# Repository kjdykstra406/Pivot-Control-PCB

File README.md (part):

"# Pivot-Control-P(kicad_sch
	(version 20250114)
	(generator "eeschema")
	(generator_version "9.0")
	(uuid "5632ba6c-34ff-4a54-b5e1-022e30e0e773")
	(paper "A0")
	(lib_symbols
		(symbol "Adafruit I2C to 8 Channel Solenoid Driver-eagle-import:DIODE-SCHOTTKYSOD-323"
			(exclude_from_sim no)
			(in_bom yes)
			(on_board yes)
			(property "Reference" "D"
				(at 0 2.54 0)
				(effects
					(font
						(size 1.27 1.0795)
					)
				)
			)
			(property "Value" ""
				(at 0 -2.5 0)
				(effects
					(font
						(size 1.27 1.0795)
					)
				)
			)
			(property "Footprint" "Adafruit I2C to 8 Channel Solenoid Driver:SOD-323"
				(at 0 0 0)
				(effects
					(font
						(size 1.27 1.27)
					)
					(hide yes)
				)
			)
			(property "Datasheet" ""
				(at 0 0 0)
				(effects
					(font
						(size 1.27 1.27)
					)
					(hide yes)
				)
			)
			(property "Description" ""
				(at 0 0 0)
				(effects
					(font
						(size 1.27 1.27)
					)
					(hide yes)
				)
			)
			(property "ki_locked" ""
				(at 0 0 0)
				(effects
					(font
						(size 1.27 1.27)
					)
				)
			)
			(symbol "DIODE-SCHOTTKYSOD-323_1_0"
				(polyline
					(pts
						(xy -1.27 1.27) (xy -1.27 -1.27)
					)
					(stroke
						(width 0.254)
						(type solid)
					)
					(fill
						(type none)
					)
				)
				(polyline
					(pts
						(xy -1.27 -1.27) (xy 1.27 0)
					)
					(stroke
						(width 0.254)
						(type solid)
					)
					(fill
						(type none)
					)
				)
				(polyline
					(pts
						(xy 1.27 1.27) (xy 0.762 1.27)
					)
					(stroke
						(width 0.254)
						(type solid)
					)
					(fill
						(type none)
					)
				)
				(polyline
					(pts
						(xy 1.27 1.27) (xy 1.27 0)
					)
					(stroke
						(width 0.254)
						(type solid)
					)
					(fill
						(type none)
					)
				)
				(polyline
					(pts
						(xy 1.27 0) (xy -1.27 1.27)
					)
					(stroke
						(width 0.254)
						(type solid)
					)
					(fill
						(type none)
					)
				)
				(polyline
					(pts
						(xy 1.27 0) (xy 1.27 -1.27)
					)
					(stroke
						(width 0.254)
						(type solid)
					)
					(fill
						(type none)
					)
				)
				(polyline
					(pts
						(xy 1.27 -1.27) (xy 1.778 -1.27)
					)
					(stroke
						(width 0.254)
						(type solid)
					)
					(fill
						(type none)
					)
				)
				(pin passive line
					(at -2.54 0 0)
					(length 2.54)
					(name "A"
						(effects
							(font
								(size 0 0)
							)
						)
					)
					(number "A"
						(effects
							(font
								(size 0 0)
							)
						)
					)
				)
				(pin passive line
					(at 2.54 0 180)
					(length 2.54)
					(name "C"
						(effects
							(font
								(size 0 0)
							)
						)
					)
					(number "C"
						(effects
							(font
								(size 0 0)
							)
						)
					)
				)
			)
			(embedded_fonts no)
		)
		(symbol "Adafruit I2C to 8 Channel Solenoid Driver-eagle-import:MOSFET-NWIDE"
			(exclude_from_sim no)
			(in_bom yes)
			(on_board yes)
			(property "Reference" "Q"
				(at 5.08 0.635 0)
				(effects
					(font
						(size 1.27 1.0795)
					)
					(justify left bottom)
				)
			)
			(property "Value" ""
				(at 5.08 -1.27 0)
				(effects
					(font
						(size 1.27 1.0795)
					)
					(justify left bottom)
				)
			)
			(property "Footprint" "Adafruit I2C to 8 Channel Solenoid Driver:SOT23-WIDE"
				(at 0 0 0)
				(effects
					(font
						(size 1.27 1.27)
					)
					(hide yes)
				)
			)
			(property "Datasheet" ""
				(at 0 0 0)
				(effects
					(font
						(size 1.27 1.27)
					)
					(hide yes)
				)
			)
			(property "Description" "N-Channel Mosfet\n\nLEGEND\n\nVDS: Voltage Drain-Source ID: Drain Current RDS(ON): Drain-Source On-State Resistance VGS(TH): Gate-Source Threshold Voltage CISS: Drain-Source Input Capacitance\n\nSOT-23   Name VDS ID RDS(ON) VGS(TH) CISS Order Number    2N7002E 60V 260mA 2.5 Ohm 2.5V @ 250uA 26.7pF @ 25V 2N7002ET1GOSTR-ND    BSH103 30V 850mA 400 mOhm 400mV @ 1mA 83pF @ 24V BSH103,235-ND    BSS138 60V 320mA 1.6 Ohm 1.5V @ 250uA 50pF @ 10V Mouser: 771-BSS138PW115    DMN2075U-7 20V 4.2A 38 mOhm 1V @ 250 uA 594.3pF @ 10V DMN2075U-7DICT-ND\n\n* BSS138 good choice for I2C level-shifting\n\nPOWERPAK 1212-8   Name VDS ID RDS(ON) VGS(TH) CISS Order Number    Si7308DN 60V 6A 58 mOhm 3V @ 250uA 665pF @ 15V SI7308DN-T1-E3CT-ND"
				(at 0 0 0)
				(effects
					(font
						(size 1.27 1.27)
					)
					(hide yes)
				)
			)
			(property "ki_locked" ""
				(at 0 0 0)
				(effects
					(font
						(size 1.27 1.27)
					)
				)
			)
			(symbol "MOSFET-NWIDE_1_0"
				(polyline
					(pts
						(xy 0 2.54) (xy 0 -2.54)
					)
					(stroke
						(width 0.254)
						(type solid)
					)
					(fill
						(type none)
					)
				)
				(polyline
					(pts
						(xy 0.762 3.175) (xy 0.762 2.54)
					)
					(stroke
						(width 0.254)
						(type solid)
					)
					(fill
						(type none)
					)
				)
				(polyline
					(pts
						(xy 0.762 2.54) (xy 0.762 1.905)
					)
					(stroke
						(width 0.254)
						(type solid)
					)
					(fill
						(type none)
					)
				)
				(polyline
					(pts
						(xy 0.762 2.54) (xy 3.81 2.54)
					)
					(stroke
						(width 0.1524)
						(type solid)
					)
					(fill
						(type none)
					)
				)
				(polyline
					(pts
						(xy 0.762 0.762) (xy 0.762 0)
					)
					(stroke
						(width 0.254)
						(type solid)
					)
					(fill
						(type none)
					)
				)
				(polyline
					(pts
						(xy 0.762 0) (xy 0.762 -0.762)
					)
					(stroke
						(width 0.254)
						(type solid)
					)
					(fill
						(type none)
					)
				)
				(polyline
					(pts
						(xy 0.762 0) (xy 2.54 0)
					)
					(stroke
						(width 0.1524)
						(type solid)
					)
					(fill
						(type none)
					)
				)
				(polyline
					(pts
						(xy 0.762 -1.905) (xy 0.762 -2.54)
					)
					(stroke
						(width 0.254)
						(type solid)
					)
					(fill
						(type none)
					)
				)
				(polyline
					(pts
						(xy 0.762 -2.54) (xy 0.762 -3.175)
					)
					(stroke
						(width 0.254)
						(type solid)
					)
					(fill
						(type none)
					)
				)
				(polyline
					(pts
						(xy 1.016 0) (xy 2.032 -0.762) (xy 2.032 0.762)
					)
					(stroke
						(width 0.1524)
						(type solid)
					)
					(fill
						(type outline)
					)
				)
				(circle
					(center 2.54 2.54)
					(radius 0.3592)
					(stroke
						(width 0)
						(type solid)
					)
					(fill
						(type none)
					)
				)
				(polyline
					(pts
						(xy 2.54 0) (xy 2.54 -2.54)
					)
					(stroke
						(width 0.1524)
						(type solid)
					)
					(fill
						(type none)
					)
				)
				(polyline
					(pts
						(xy 2.54 -2.54) (xy 0.762 -2.54)
					)
					(stroke
						(width 0.1524)
						(type solid)
					)
					(fill
						(type none)
					)
				)
				(polyline
					(pts
						(xy 2.54 -2.54) (xy 3.81 -2.54)
					)
					(stroke
						(width 0.1524)
						(type solid)
					)
					(fill
						(type none)
					)
				)
				(circle
					(center 2.54 -2.54)
					(radius 0.3592)
					(stroke
						(width 0)
						(type solid)
					)
					(fill
						(type none)
					)
				)
				(polyline
					(pts
						(xy 3.302 0.508) (xy 3.048 0.254)
					)
					(stroke
						(width 0.1524)
						(type solid)
					)
					(fill
						(type none)
					)
				)
				(polyline
					(pts
						(xy 3.81 2.54) (xy 3.81 0.508)
					)
					(stroke
						(width 0.1524)
						(type solid)
					)
					(fill
						(type none)
					)
				)
				(polyline
					(pts
						(xy 3.81 0.508) (xy 3.302 0.508)
					)
					(stroke
						(width 0.1524)
						(type solid)
					)
					(fill
						(type none)
					)
				)
				(polyline
					(pts
						(xy 3.81 0.508) (xy 3.81 -2.54)
					)
					(stroke
						(width 0.1524)
						(type solid)
					)
					(fill
						(type none)
					)
				)
				(polyline
					(pts
						(xy 3.81 -0.508) (xy 3.302 0.254) (xy 4.318 0.254)
					)
					(stroke
						(width 0.1524)
						(type solid)
					)
					(fill
						(type outline)
					)
				)
				(polyline
					(pts
						(xy 4.318 0.508) (xy 3.81 0.508)
					)
					(stroke
						(width 0.1524)
						(type solid)
					)
					(fill
						(type none)
					)
				)
				(polyline
					(pts
						(xy 4.572 0.762) (xy 4.318 0.508)
					)
					(stroke
						(width 0.1524)
						(type solid)
					)
					(fill
						(type none)
					)
				)
				(text "G"
					(at -1.27 -1.905 0)
					(effects
						(font
							(size 0.8128 0.6908)
						)
						(justify left bottom)
					)
				)
				(text "D"
					(at 3.175 3.175 0)
					(effects
						(font
							(size 0.8128 0.6908)
						)
						(justify left bottom)
					)
				)
				(text "S"
					(at 3.175 -3.81 0)
					(effects
						(font
							(size 0.8128 0.6908)
						)
						(justify left bottom)
					)
				)
				(pin bidirectional line
					(at -2.54 -2.54 0)
					(length 2.54)
					(name "G"
						(effects
							(font
								(size 0 0)
							)
						)
					)
					(number "1"
						(effects
							(font
								(size 1.524 1.524)
							)
						)
					)
				)
				(pin bidirectional line
					(at 2.54 5.08 270)
					(length 2.54)
					(name "D"
						(effects
							(font
								(size 0 0)
							)
						)
					)
					(number "3"
						(effects
							(font
								(size 1.524 1.524)
							)
						)
					)
				)
				(pin bidirectional line
					(at 2.54 -5.08 90)
					(length 2.54)
					(name "S"
						(effects
							(font
								(size 0 0)
							)
						)
					)
					(number "2"
						(effects
							(font
								(size 1.524 1.524)
							)
						)
					)
				)
			)
			(embedded_fonts no)
		)
		(symbol "Adafruit I2C to 8 Channel Solenoid Driver-eagle-import:RESISTOR_0603_NOOUT"
			(exclude_from_sim no)
			(in_bom yes)
			(on_board yes)
			(property "Reference" "R"
				(at 0 2.54 0)
				(effects
					(font
						(size 1.27 1.27)
					)
				)
			)
			(property "Value" ""
				(at 0 0 0)
				(effects
					(font
						(size 1.016 1.016)
						(thickness 0.2032)
						(bold yes)
					)
				)
			)
			(property "Footprint" "Adafruit I2C to 8 Channel Solenoid Driver:0603-NO"
				(at 0 0 0)
				(effects
					(font
						(size 1.27 1.27)
					)
					(hide yes)
				)
			)
			(property "Datasheet" ""
				(at 0 0 0)
				(effects
					(font
						(size 1.27 1.27)
					)
					(hide yes)
				)
			)
			(property "Description" "Resistors\n\nFor new designs, use the packages preceded by an '_' character since they are more reliable:\n\nThe following footprints should be used on most boards:\n\n• _0402 - Standard footprint for regular board layouts\n• _0603 - Standard footprint for regular board layouts\n• _0805 - Standard footprint for regular board layouts\n• _1206 - Standard footprint for regular board layouts\n\nFor extremely tight-pitch boards where space is at a premium, the following 'micro-pitch' footprints can be used (smaller pads, no silkscreen outline, etc.):\n\n• _0402MP - Micro-pitch footprint for very dense/compact boards\n• _0603MP - Micro-pitch footprint for very dense/compact boards\n• _0805MP - Micro-pitch footprint for very dense/compact boards\n• _1206MP - Micro-pitch footprint for very dense/compact boards"
				(at 0 0 0)
				(effects
					(font
						(size 1.27 1.27)
					)
					(hide yes)
				)
			)
			(property "ki_locked" ""
				(at 0 0 0)
				(effects
					(font
						(size 1.27 1.27)
					)
				)
			)
			(symbol "RESISTOR_0603_NOOUT_1_0"
				(polyline
					(pts
						(xy -2.54 1.27) (xy 2.54 1.27)
					)
					(stroke
						(width 0.254)
						(type solid)
					)
					(fill
						(type none)
					)
				)
				(polyline
					(pts
						(xy -2.54 -1.27) (xy -2.54 1.27)
					)
					(stroke
						(width 0.254)
						(type solid)
					)
					(fill
						(type none)
					)
				)
				(polyline
					(pts
						(xy 2.54 1.27) (xy 2.54 -1.27)
					)
					(stroke
						(width 0.254)
						(type solid)
					)
					(fill
						(type none)
					)
				)
				(polyline
					(pts
						(xy 2.54 -1.27) (xy -2.54 -1.27)
					)
					(stroke
						(width 0.254)
						(type solid)
					)
					(fill
						(type none)
					)
				)
				(pin passive line
					(at -5.08 0 0)
					(length 2.54)
					(name "1"
						(effects
							(font
								(size 0 0)
							)
						)
					)
					(number "1"
						(effects
							(font
								(size 0 0)
							)
						)
					)
				)
				(pin passive line
					(at 5.08 0 180)
					(length 2.54)
					(name "2"
						(effects
							(font
								(size 0 0)
							)
						)
					)
					(number "2"
						(effects
							(font
								(size 0 0)
							)
						)
					)
				)
			)
			(embedded_fonts no)
		)
		(symbol "Adafruit I2C to 8 Channel Solenoid Driver-eagle-import:V+"
			(power)
			(exclude_from_sim no)
			(in_bom yes)
			(on_board yes)
			(property "Reference" "#P+"
				(at 0 0 0)
				(effects
					(font
						(size 1.27 1.27)
					)
					(hide yes)
				)
			)
			(property "Value" ""
				(at -2.54 -2.54 90)
				(effects
					(font
						(size 1.778 1.5113)
					)
					(justify left bottom)
				)
			)
			(property "Footprint" ""
				(at 0 0 0)
				(effects
					(font
						(size 1.27 1.27)
					)
					(hide yes)
				)
			)
			(property "Datasheet" ""
				(at 0 0 0)
				(effects
					(font
						(size 1.27 1.27)
					)
					(hide yes)
				)
			)
			(property "Description" "SUPPLY SYMBOL"
				(at 0 0 0)
				(effects
					(font
						(size 1.27 1.27)
					)
					(hide yes)
				)
			)
			(property "ki_locked" ""
				(at 0 0 0)
				(effects
					(font
						(size 1.27 1.27)
					)
				)
			)
			(symbol "V+_1_0"
				(polyline
					(pts
						(xy -0.889 -1.27) (xy 0.889 -1.27)
					)
					(stroke
						(width 0.254)
						(type solid)
					)
					(fill
						(type none)
					)
				)
				(polyline
					(pts
						(xy 0 0.127) (xy -0.889 -1.27)
					)
					(stroke
						(width 0.254)
						(type solid)
					)
					(fill
						(type none)
					)
				)
				(polyline
					(pts
						(xy 0.889 -1.27) (xy 0 0.127)
					)
					(stroke
						(width 0.254)
						(type solid)
					)
					(fill
						(type none)
					)
				)
				(pin power_in line
					(at 0 -2.54 90)
					(length 2.54)
					(name "V+"
						(effects
							(font
								(size 0 0)
							)
						)
					)
					(number "1"
						(effects
							(font
								(size 0 0)
							)
						)
					)
				)
			)
			(embedded_fonts no)
		)
		(symbol "Adafruit I2C to 8 Channel Solenoid Driver-eagle-import:supply1_371_GND"
			(power)
			(exclude_from_sim no)
			(in_bom yes)
			(on_board yes)
			(property "Reference" "#GND"
				(at 0 0 0)
				(effects
					(font
						(size 1.27 1.27)
					)
					(hide yes)
				)
			)
			(property "Value" ""
				(at -2.54 -2.54 0)
				(effects
					(font
						(size 1.778 1.5113)
					)
					(justify left bottom)
				)
			)
			(property "Footprint" ""
				(at 0 0 0)
				(effects
					(font
						(size 1.27 1.27)
					)
					(hide yes)
				)
			)
			(property "Datasheet" ""
				(at 0 0 0)
				(effects
					(font
						(size 1.27 1.27)
					)
					(hide yes)
				)
			)
			(property "Description" "SUPPLY SYMBOL"
				(at 0 0 0)
				(effects
					(font
						(size 1.27 1.27)
					)
					(hide yes)
				)
			)
			(property "ki_locked" ""
				(at 0 0 0)
				(effects
					(font
						(size 1.27 1.27)
					)
				)
			)
			(symbol "supply1_371_GND_1_0"
				(polyline
					(pts
						(xy -1.905 0) (xy 1.905 0)
					)
					(stroke
						(width 0.254)
						(type solid)
					)
					(fill
						(type none)
					)
				)
				(pin power_in line
					(at 0 2.54 270)
					(length 2.54)
					(name "GND"
						(effects
							(font
								(size 0 0)
							)
						)
					)
					(number "1"
						(effects
							(font
								(size 0 0)
							)
						)
					)
				)
			)
			(embedded_fonts no)
		)
		(symbol "Pivot PCB:G6RN-1_DC5"
			(pin_names
				(offset 0.254)
			)
			(exclude_from_sim no)
			(in_bom yes)
			(on_board yes)
			(property "Reference" "K"
				(at 20.32 10.16 0)
				(effects
					(font
						(size 1.524 1.524)
					)
				)
			)
			(property "Value" "G6RN-1 DC5"
				(at 20.32 7.62 0)
				(effects
					(font
						(size 1.524 1.524)
					)
				)
			)
			(property "Footprint" "RELAY_G6RN-1_OMR"
				(at 0 0 0)
				(effects
					(font
						(size 1.27 1.27)
						(italic yes)
					)
					(hide yes)
				)
			)
			(property "Datasheet" "G6RN-1 DC5"
				(at 0 0 0)
				(effects
					(font
						(size 1.27 1.27)
						(italic yes)
					)
					(hide yes)
				)
			)
			(property "Description" ""
				(at 0 0 0)
				(effects
					(font
						(size 1.27 1.27)
					)
					(hide yes)
				)
			)
			(property "ki_locked" ""
				(at 0 0 0)
				(effects
					(font
						(size 1.27 1.27)
					)
				)
			)
			(property "ki_keywords" "G6RN-1 DC5"
				(at 0 0 0)
				(effects
					(font
						(size 1.27 1.27)
					)
					(hide yes)
				)
			)
			(property "ki_fp_filters" "RELAY_G6RN-1_OMR"
				(at 0 0 0)
				(effects
					(font
						(size 1.27 1.27)
					)
					(hide yes)
				)
			)
			(symbol "G6RN-1_DC5_0_1"
				(polyline
					(pts
						(xy 7.62 5.08) (xy 7.62 -10.16)
					)
					(stroke
						(width 0.127)
						(type default)
					)
					(fill
						(type none)
					)
				)
				(polyline
					(pts
						(xy 7.62 -3.175) (xy 20.32 -3.175)
					)
					(stroke
						(width 0.127)
						(type default)
					)
					(fill
						(type none)
					)
				)
				(polyline
					(pts
						(xy 7.62 -10.16) (xy 33.02 -10.16)
					)
					(stroke
						(width 0.127)
						(type default)
					)
					(fill
						(type none)
					)
				)
				(polyline
					(pts
						(xy 19.685 1.905) (xy 20.955 1.905)
					)
					(stroke
						(width 0.127)
						(type default)
					)
					(fill
						(type none)
					)
				)
				(polyline
					(pts
						(xy 19.685 1.27) (xy 19.685 1.905)
					)
					(stroke
						(width 0.127)
						(type default)
					)
					(fill
						(type none)
					)
				)
				(polyline
					(pts
						(xy 19.685 0.635) (xy 7.62 0.635)
					)
					(stroke
						(width 0.127)
						(type default)
					)
					(fill
						(type none)
					)
				)
				(polyline
					(pts
						(xy 19.685 -0.635) (xy 19.685 1.27)
					)
					(stroke
						(width 0.127)
						(type default)
					)
					(fill
						(type none)
					)
				)
				(polyline
					(pts
						(xy 20.32 -5.08) (xy 20.32 -3.175)
					)
					(stroke
						(width 0.127)
						(type default)
					)
					(fill
						(type none)
					)
				)
				(polyline
					(pts
						(xy 20.32 -5.08) (xy 24.765 -5.08)
					)
					(stroke
						(width 0.127)
						(type default)
					)
					(fill
						(type none)
					)
				)
				(polyline
					(pts
						(xy 20.955 1.905) (xy 20.955 -0.635)
					)
					(stroke
						(width 0.127)
						(type default)
					)
					(fill
						(type none)
					)
				)
				(polyline
					(pts
						(xy 20.955 0.635) (xy 33.02 0.635)
					)
					(stroke
						(width 0.127)
						(type default)
					)
					(fill
						(type none)
					)
				)
				(polyline
					(pts
						(xy 20.955 -0.635) (xy 19.685 -0.635)
					)
					(stroke
						(width 0.127)
						(type default)
					)
					(fill
						(type none)
					)
				)
				(polyline
					(pts
						(xy 24.765 -5.08) (xy 27.305 -4.445)
					)
					(stroke
						(width 0.127)
						(type default)
					)
					(fill
						(type none)
					)
				)
				(polyline
					(pts
						(xy 26.035 -3.81) (xy 26.67 -4.445)
					)
					(stroke
						(width 0.127)
						(type default)
					)
					(fill
						(type none)
					)
				)
				(polyline
					(pts
						(xy 26.035 -3.81) (xy 27.305 -3.81)
					)
					(stroke
						(width 0.127)
						(type default)
					)
					(fill
						(type none)
					)
				)
				(polyline
					(pts
						(xy 26.035 -3.81) (xy 27.305 -3.81) (xy 26.67 -4.445) (xy 26.035 -3.81)
					)
					(stroke
						(width 0)
						(type default)
					)
					(fill
						(type outline)
					)
				)
				(polyline
					(pts
						(xy 26.035 -6.35) (xy 26.67 -5.715)
					)
					(stroke
						(width 0.127)
						(type default)
					)
					(fill
						(type none)
					)
				)
				(polyline
					(pts
						(xy 26.035 -6.35) (xy 27.305 -6.35)
					)
					(stroke
						(width 0.127)
						(type default)
					)
					(fill
						(type none)
					)
				)
				(polyline
					(pts
						(xy 26.035 -6.35) (xy 26.67 -5.715) (xy 27.305 -6.35)
					)
					(stroke
						(width 0)
						(type default)
					)
					(fill
						(type outline)
					)
				)
				(polyline
					(pts
						(xy 26.67 -3.81) (xy 26.67 -3.175)
					)
					(stroke
						(width 0.127)
						(type default)
					)
					(fill
						(type none)
					)
				)
				(polyline
					(pts
						(xy 26.67 -6.985) (xy 26.67 -6.35)
					)
					(stroke
						(width 0.127)
						(type default)
					)
					(fill
						(type none)
					)
				)
				(polyline
					(pts
						(xy 27.305 -3.81) (xy 26.67 -4.445)
					)
					(stroke
						(width 0.127)
						(type default)
					)
					(fill
						(type none)
					)
				)
				(polyline
					(pts
						(xy 27.305 -6.35) (xy 26.67 -5.715)
					)
					(stroke
						(width 0.127)
						(type default)
					)
					(fill
						(type none)
					)
				)
				(polyline
					(pts
						(xy 33.02 5.08) (xy 7.62 5.08)
					)
					(stroke
						(width 0.127)
						(type default)
					)
					(fill
						(type none)
					)
				)
				(polyline
					(pts
						(xy 33.02 -3.175) (xy 26.67 -3.175)
					)
					(stroke
						(width 0.127)
						(type default)
					)
					(fill
						(type none)
					)
				)
				(polyline
					(pts
						(xy 33.02 -6.985) (xy 26.67 -6.985)
					)
					(stroke
						(width 0.127)
						(type default)
					)
					(fill
						(type none)
					)
				)
				(polyline
					(pts
						(xy 33.02 -10.16) (xy 33.02 5.08)
					)
					(stroke
						(width 0.127)
						(type default)
					)
					(fill
						(type none)
					)
				)
				(pin unspecified line
					(at 0 0.635 0)
					(length 7.62)
					(name "1"
						(effects
							(font
								(size 1.27 1.27)
							)
						)
					)
					(number "1"
						(effects
							(font
								(size 1.27 1.27)
							)
						)
					)
				)
				(pin unspecified line
					(at 0 -3.175 0)
					(length 7.62)
					(name "2"
						(effects
							(font
								(size 1.27 1.27)
							)
						)
					)
					(number "2"
						(effects
							(font
								(size 1.27 1.27)
							)
						)
					)
				)
				(pin unspecified line
					(at 40.64 0.635 180)
					(length 7.62)
					(name "5"
						(effects
							(font
								(size 1.27 1.27)
							)
						)
					)
					(number "5"
						(effects
							(font
								(size 1.27 1.27)
							)
						)
					)
				)
				(pin unspecified line
					(at 40.64 -3.175 180)
					(length 7.62)
					(name "4"
						(effects
							(font
								(size 1.27 1.27)
							)
						)
					)
					(number "4"
						(effects
							(font
								(size 1.27 1.27)
							)
						)
					)
				)
				(pin unspecified line
					(at 40.64 -6.985 180)
					(length 7.62)
					(name "3"
						(effects
							(font
								(size 1.27 1.27)
							)
						)
					)
					(number "3"
						(effects
							(font
								(size 1.27 1.27)
							)
						)
					)
				)
			)
			(embedded_fonts no)
		)
		(symbol "Pivot PCB:Screw_Terminal_01x20"
			(pin_names
				(offset 1.016)
				(hide yes)
			)
			(exclude_from_sim no)
			(in_bom yes)
			(on_board yes)
			(property "Reference" "J"
				(at 0 25.4 0)
				(effects
					(font
						(size 1.27 1.27)
					)
				)
			)
			(property "Value" "Screw_Terminal_01x20"
				(at 0 -27.94 0)
				(effects
					(font
						(size 1.27 1.27)
					)
				)
			)
			(property "Footprint" ""
				(at 0 0 0)
				(effects
					(font
						(size 1.27 1.27)
					)
					(hide yes)
				)
			)
			(property "Datasheet" "~"
				(at 0 0 0)
				(effects
					(font
						(size 1.27 1.27)
					)
					(hide yes)
				)
			)
			(property "Description" "Generic screw terminal, single row, 01x20, script generated (kicad-library-utils/schlib/autogen/connector/)"
				(at 0 0 0)
				(effects
					(font
						(size 1.27 1.27)
					)
					(hide yes)
				)
			)
			(property "ki_keywords" "screw terminal"
				(at 0 0 0)
				(effects
					(font
						(size 1.27 1.27)
					)
					(hide yes)
				)
			)
			(property "ki_fp_filters" "TerminalBlock*:*"
				(at 0 0 0)
				(effects
					(font
						(size 1.27 1.27)
					)
					(hide yes)
				)
			)
			(symbol "Screw_Terminal_01x20_1_1"
				(rectangle
					(start -1.27 24.13)
					(end 1.27 -26.67)
					(stroke
						(width 0.254)
						(type default)
					)
					(fill
						(type background)
					)
				)
				(polyline
					(pts
						(xy -0.5334 23.1902) (xy 0.3302 22.352)
					)
					(stroke
						(width 0.1524)
						(type default)
					)
					(fill
						(type none)
					)
				)
				(polyline
					(pts
						(xy -0.5334 20.6502) (xy 0.3302 19.812)
					)
					(stroke
						(width 0.1524)
						(type default)
					)
					(fill
						(type none)
					)
				)
				(polyline
					(pts
						(xy -0.5334 18.1102) (xy 0.3302 17.272)
					)
					(stroke
						(width 0.1524)
						(type default)
					)
					(fill
						(type none)
					)
				)
				(polyline
					(pts
						(xy -0.5334 15.5702) (xy 0.3302 14.732)
					)
					(stroke
						(width 0.1524)
						(type default)
					)
					(fill
						(type none)
					)
				)
				(polyline
					(pts
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
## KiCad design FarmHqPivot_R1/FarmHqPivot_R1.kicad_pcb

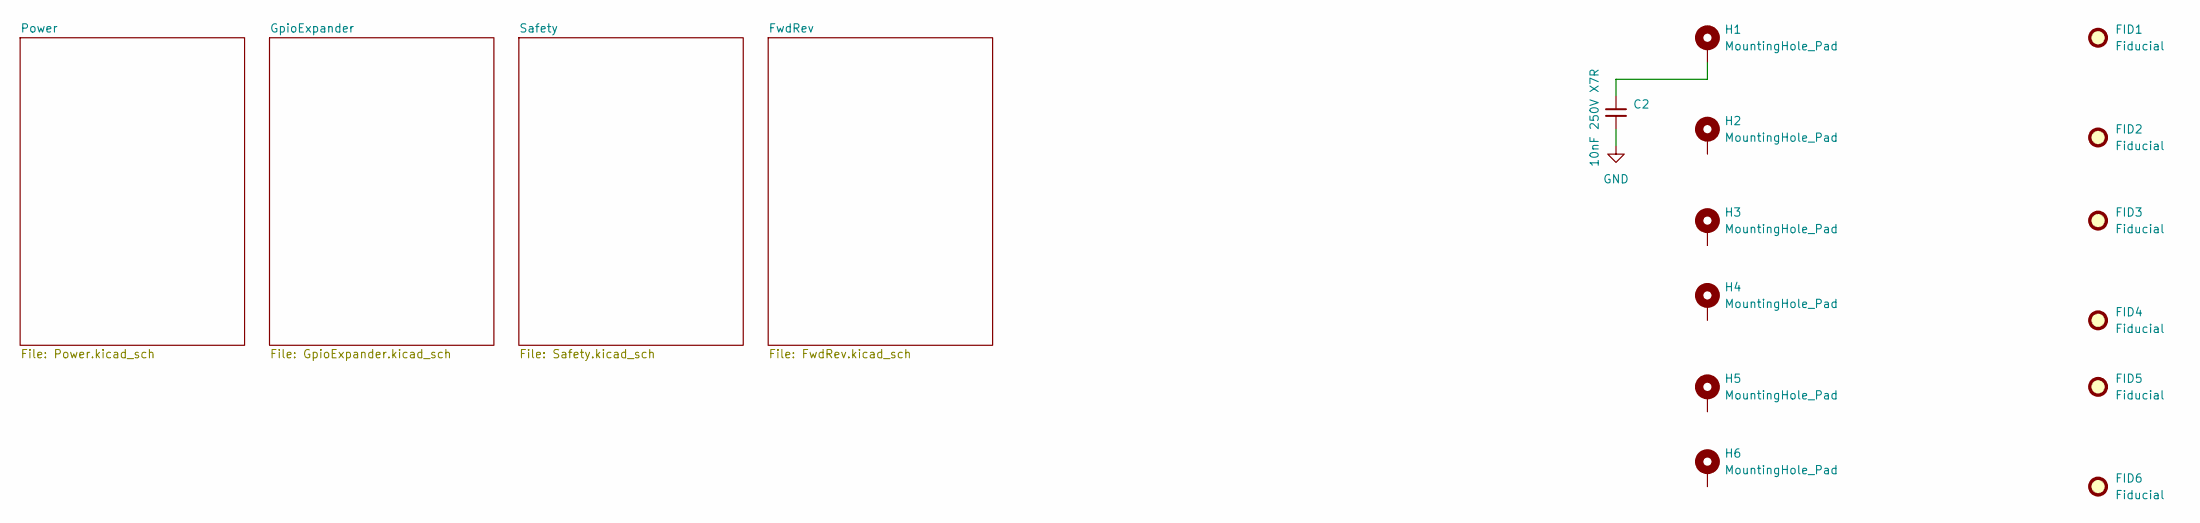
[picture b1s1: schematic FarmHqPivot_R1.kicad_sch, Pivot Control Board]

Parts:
C2: 10nF 250V X7R; C_1206_3216Metric; Digikey 399-C1206C103KARECTUDKR-ND
FID1, FID2, FID3, FID4, FID5, FID6: Fiducial; Fiducial_1mm_Mask2mm
H1, H2, H3, H4, H5, H6: MountingHole_Pad; MountingHole_3.5mm_Pad

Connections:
GND: C2.2; also elsewhere on the board
unnamed: C2.1, H1.1 (1_1)

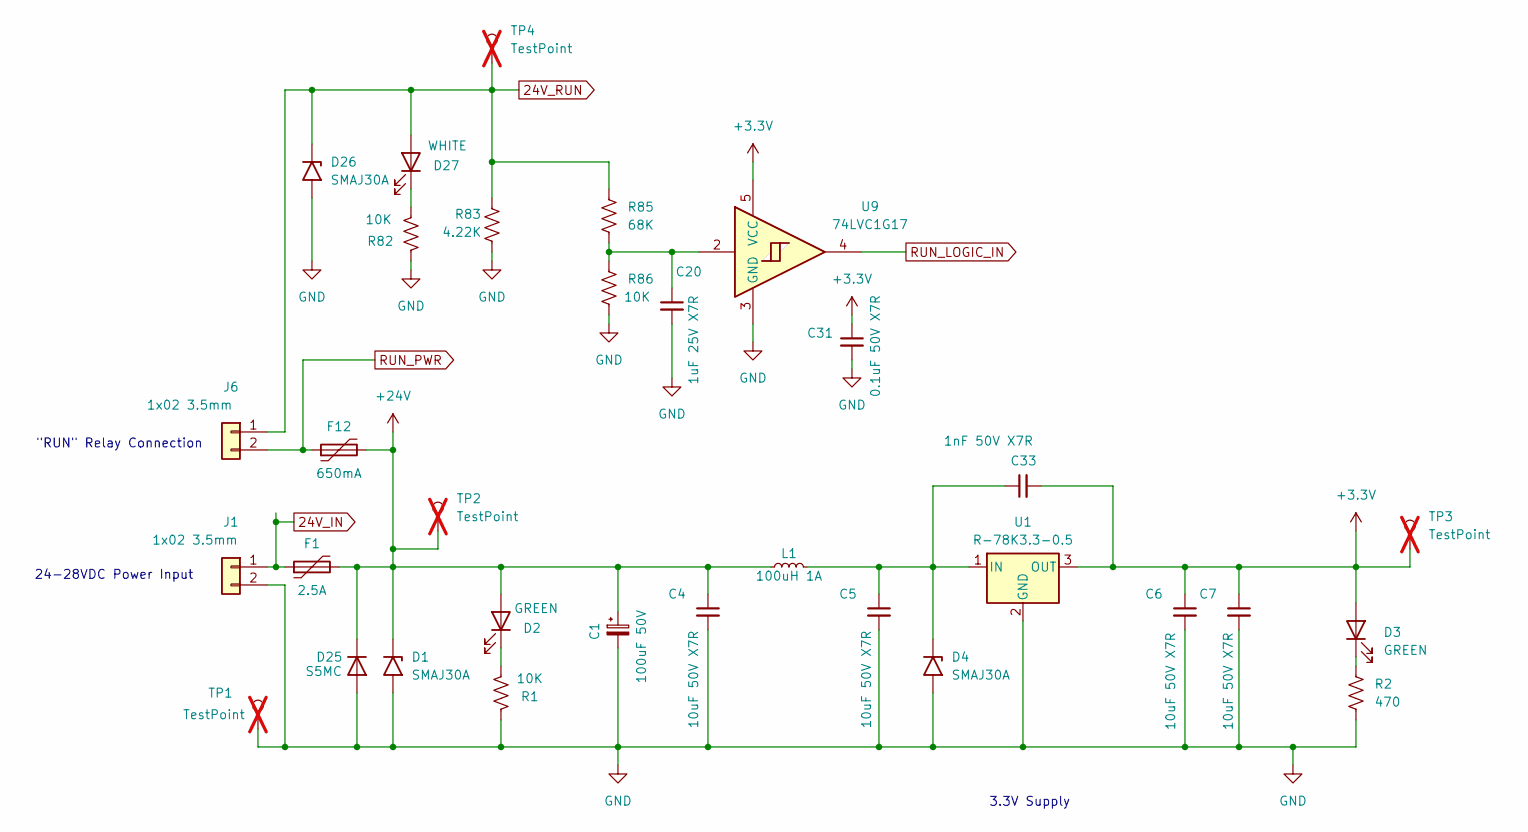
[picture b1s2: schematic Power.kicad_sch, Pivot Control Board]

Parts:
C1: 100uF 50V; CP_Elec_6.3x7.7; Digikey PCE5024DKR-ND
C4, C5, C6, C7: 10uF 50V X7R; C_1210_3225Metric; Digikey 1276-7052-6-ND
C20: 1uF 25V X7R; C_0603_1608Metric; Digikey 399-C0603C105K3RACTUDKR-ND
C31: 0.1uF 50V X7R; C_0603_1608Metric; Digikey 399-C0603C104K5RACTUDKR-ND
C33: 1nF 50V X7R; C_0805_2012Metric; Digikey 399-C0805C102K5HACAUTODKR-ND
D1, D4, D26: SMAJ30A; D_SMA; Manufacturer PN SMAJ30A; Digikey SMAJ30ALFDKR-ND
D2, D3: GREEN; LED_0603_1608Metric; Manufacturer PN 5991060147F; Digikey 350-5991060147FDKR-ND
D25: S5MC; D_SMC; Manufacturer PN S5MC-13-F; Digikey S5MC-FDIDKR-ND
D27: WHITE; LED_0603_1608Metric; Manufacturer PN 598-2002-107F; Digikey 350-598-2002-107FDKR-ND
F1: 2.5A; Fuse_Bourns_MF-RHT1100; Manufacturer PN RXEF250; Digikey RXEF250HF-ND
F12: 650mA; Fuse_Bourns_MF-RHT100; Manufacturer PN MF-R065; Digikey MF-R065-ND
J1, J6: 1x02 3.5mm; TerminalBlock_Phoenix_PT-1,5-2-3.5-H_1x02_P3.50mm_Horizontal; Manufacturer PN 1984617; Digikey 277-1721-ND
L1: 100uH 1A; L_TDK_SLF7045; Manufacturer PN SRR7045-101M; Digikey 118-SRR7045-101MDKR-ND
R1, R82: 10K; R_0805_2012Metric; Digikey 311-10.0KCRDKR-ND
R2: 470; R_0603_1608Metric; Digikey 311-470HRDKR-ND
R83: 4.22K; R_2010_5025Metric; Digikey 541-4.22KACDKR-ND
R85: 68K; R_0603_1608Metric; Digikey 311-68.0KHRDKR-ND
R86: 10K; R_0603_1608Metric; Digikey 311-10KLDDKR-ND
TP1, TP2, TP3, TP4: TestPoint; TestPoint_Keystone_5015_Micro_Mini; not fitted
U1: R-78K3.3-0.5; Converter_DCDC_RECOM_R-78E-0.5_THT; Manufacturer PN R-78K3.3-0.5; Digikey 945-R-78K3.3-0.5-ND
U9: 74LVC1G17; SOT-23-5; Manufacturer PN SN74LVC1G17DBVR; Digikey 296-11933-6-ND

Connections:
24V_IN: F1.1, J1.1
24V_RUN: D26.1 (A1), D27.2 (A), J6.1, R83.1, R85.1, TP4.1 (1_1); also elsewhere on the board
+3.3V: C6.1, C7.1, C31.1, C33.2, D3.2 (A), TP3.1 (1_1), U1.3 (OUT), U9.5 (VCC); also elsewhere on the board
+24V: C1.1, C4.1, D1.1 (A1), D2.2 (A), D25.1 (K), F1.2, F12.2, L1.2, TP2.1 (1_1); also elsewhere on the board
GND: C1.2, C4.2, C5.2, C6.2, C7.2, C20.2, C31.2, D1.2 (A2), D4.2 (A2), D25.2 (A), D26.2 (A2), J1.2, R1.2, R2.2, R82.2, R83.2, R86.2, TP1.1 (1_1), U1.2 (GND), U9.3 (GND); also elsewhere on the board
unnamed: C20.1, R85.2, R86.1, U9.2
unnamed: D2.1 (K), R1.1
unnamed: D3.1 (K), R2.1
unnamed: C5.1, C33.1, D4.1 (A1), L1.1, U1.1 (IN)
unnamed: D27.1 (K), R82.1
RUN_LOGIC_IN: U9.4; also elsewhere on the board
RUN_PWR: F12.1, J6.2; also elsewhere on the board

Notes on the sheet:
"RUN" Relay Connection
24-28VDC Power Input
3.3V Supply

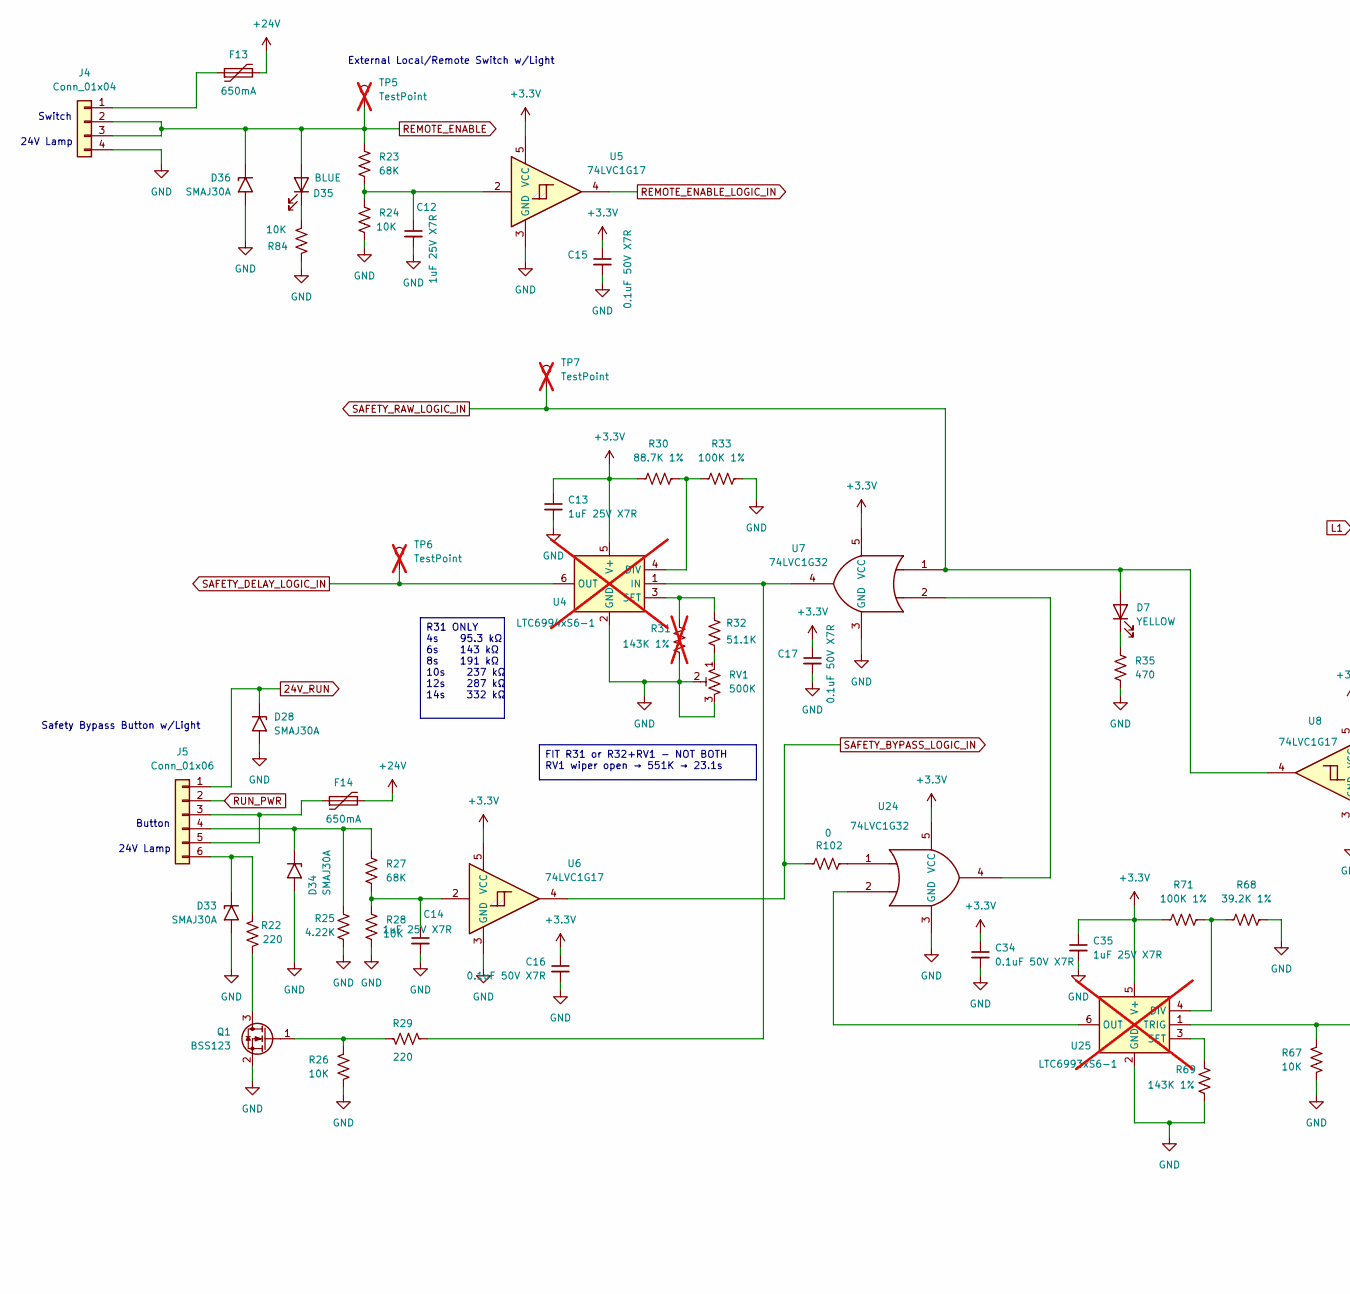
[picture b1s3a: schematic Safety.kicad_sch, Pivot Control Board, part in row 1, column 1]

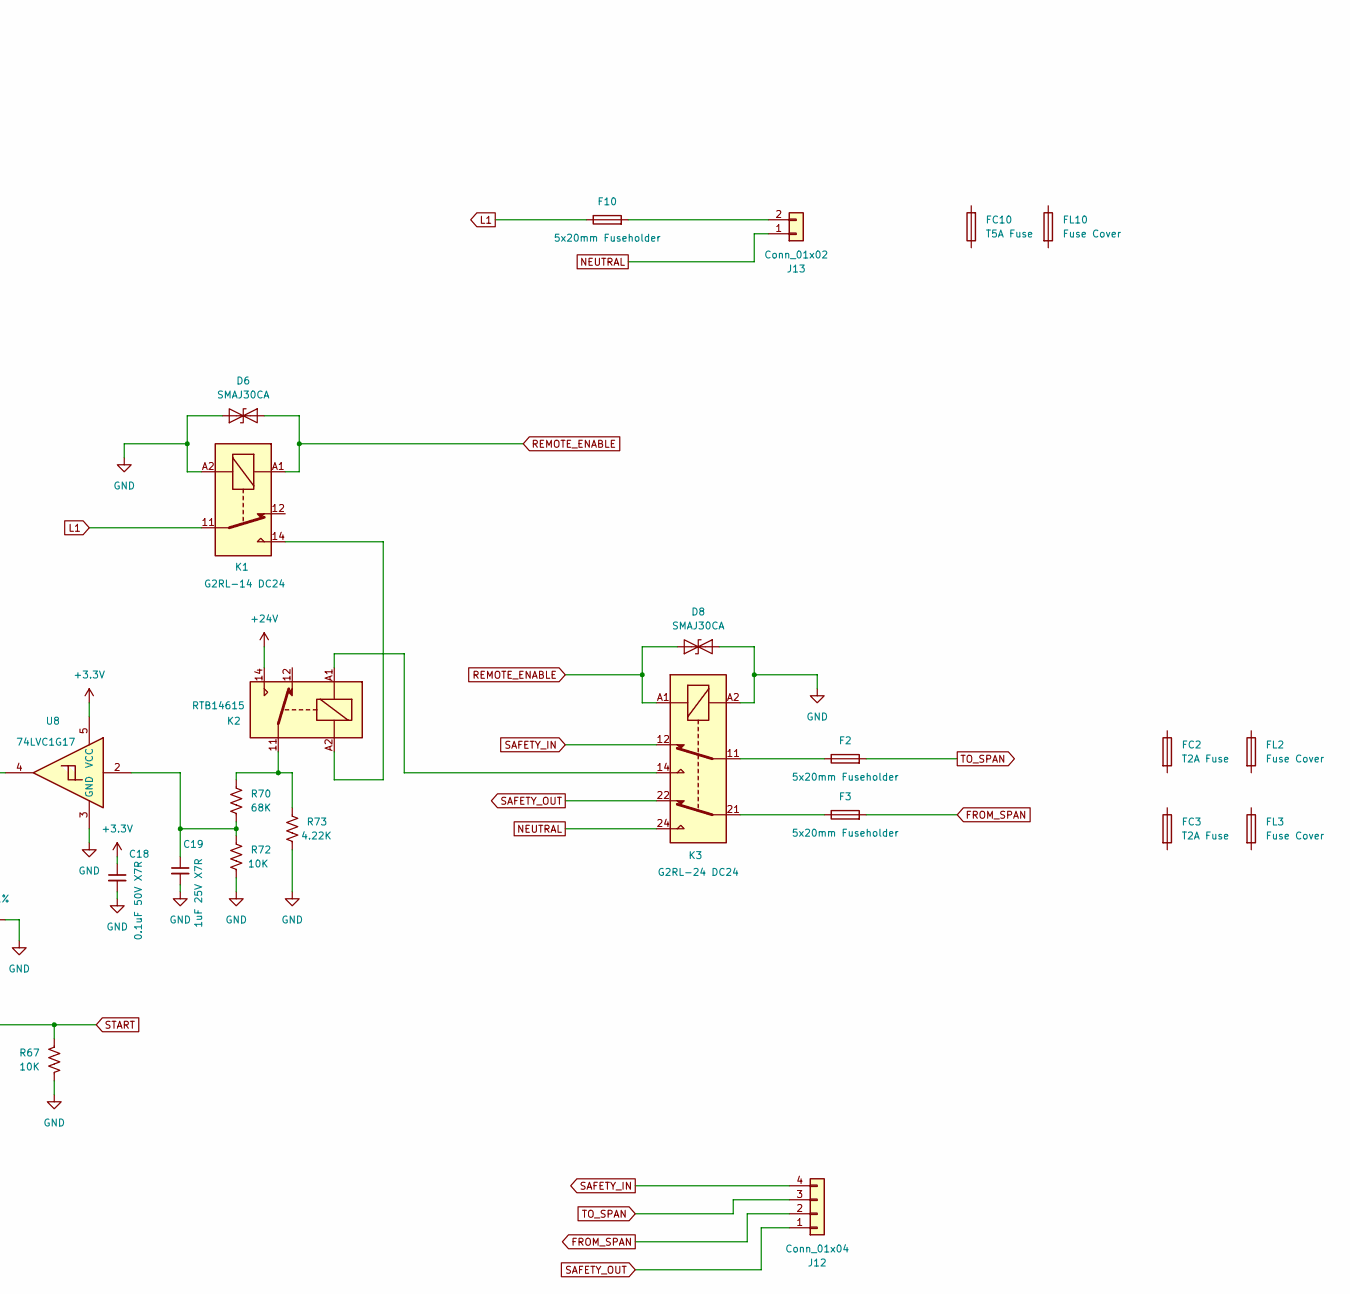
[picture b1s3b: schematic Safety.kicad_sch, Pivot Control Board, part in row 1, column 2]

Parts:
C12, C13, C14, C19, C35: 1uF 25V X7R; C_0603_1608Metric; Digikey 399-C0603C105K3RACTUDKR-ND
C15, C16, C17, C18, C34: 0.1uF 50V X7R; C_0603_1608Metric; Digikey 399-C0603C104K5RACTUDKR-ND
D6, D8: SMAJ30CA; D_SMA; Manufacturer PN SMAJ30CA; Digikey SMAJ30CALFDKR-ND
D7: YELLOW; LED_0603_1608Metric; Manufacturer PN 5991040147F; Digikey 350-5991040147FDKR-ND
D28, D33, D34, D36: SMAJ30A; D_SMA; Manufacturer PN SMAJ30A; Digikey SMAJ30ALFDKR-ND
D35: BLUE; LED_0603_1608Metric; Manufacturer PN 5991090147F; Digikey 350-5991090147FDKR-ND
F2, F3, F10: 5x20mm Fuseholder; 696105003002; Manufacturer PN 696105003002; Digikey 732-11373-ND
F13, F14: 650mA; Fuse_Bourns_MF-RHT100; Manufacturer PN MF-R065; Digikey MF-R065-ND
FC2, FC3: T2A Fuse; Manufacturer PN 5HT 2-R; Digikey 5923-5HT2-R-ND
FC10: T5A Fuse; Manufacturer PN 5HT 5-R; Digikey 5923-5HT5-R-ND
FL2, FL3, FL10: Fuse Cover; Manufacturer PN 696122003001; Digikey 732-11379-ND
J4: Conn_01x04; TerminalBlock_Phoenix_PT-1,5-4-3.5-H_1x04_P3.50mm_Horizontal; Manufacturer PN 1984633; Digikey 277-1860-ND
J5: Conn_01x06; TerminalBlock_Phoenix_PT-1,5-6-3.5-H_1x06_P3.50mm_Horizontal; Manufacturer PN 1984659; Digikey 277-1724-ND
J12: Conn_01x04; TerminalBlock_Phoenix_PT-1,5-4-5.0-H_1x04_P5.00mm_Horizontal; Manufacturer PN 1935187; Digikey 277-1579-ND
J13: Conn_01x02; TerminalBlock_Phoenix_PT-1,5-2-5.0-H_1x02_P5.00mm_Horizontal; Manufacturer PN 1935161; Digikey 277-1667-ND
K1: G2RL-14 DC24; Relay_SPDT_Finder_40.31; Manufacturer PN G2RL-14 DC24; Digikey Z144-ND
K2: RTB14615; Relay_SPDT_Schrack-RT1-FormC_RM3.5mm; Manufacturer PN RTB14615; Digikey PB977-ND
K3: G2RL-24 DC24; Relay_DPDT_Finder_40.52; Manufacturer PN G2RL-24 DC24; Digikey Z148-ND
Q1: BSS123; SOT-23; Manufacturer PN BSS123; Digikey BSS123NDKR-ND
R22: 220; R_1206_3216Metric; Digikey A130530DKR-ND
R23, R27, R70: 68K; R_0603_1608Metric; Digikey 311-68.0KHRDKR-ND
R24, R26, R28, R67, R72: 10K; R_0603_1608Metric; Digikey 311-10KLDDKR-ND
R25, R73: 4.22K; R_2010_5025Metric; Digikey 541-4.22KACDKR-ND
R29: 220; R_0603_1608Metric; Digikey 311-220HRDKR-ND
R30: 88.7K 1%; R_0603_1608Metric; Digikey 311-88.7KHRDKR-ND
R31: 143K 1%; R_0603_1608Metric; Digikey 13-RC0603FR-13143KLDKR-ND; not fitted
R32: 51.1K; R_0603_1608Metric; Digikey 311-51.1KHRDKR-ND
R33, R71: 100K 1%; R_0603_1608Metric; Digikey 311-100KHRDKR-ND
R35: 470; R_0603_1608Metric; Digikey 311-470HRDKR-ND
R68: 39.2K 1%; R_0603_1608Metric; Digikey 311-39.2KHRDKR-ND
R69: 143K 1%; R_0603_1608Metric; Digikey 13-RC0603FR-13143KLDKR-ND
R84: 10K; R_0805_2012Metric; Digikey 311-10.0KCRDKR-ND
R102: 0; R_0603_1608Metric; Digikey 311-0.0GRDKR-ND
RV1: 500K; Potentiometer_Bourns_3266Y_Vertical; Manufacturer PN 3266Y-1-504LF; Digikey 3266Y-1-504LF-ND
TP5, TP6, TP7: TestPoint; TestPoint_Keystone_5015_Micro_Mini; not fitted
U4: LTC6994xS6-1; TSOT-23-6; Manufacturer PN LTC6994HS6-1#TRMPBF; Digikey 505-LTC6994HS6-1#WTRMPBFDKR-ND; not fitted
U5, U6, U8: 74LVC1G17; SOT-23-5; Manufacturer PN SN74LVC1G17DBVR; Digikey 296-11933-6-ND
U7, U24: 74LVC1G32; SOT-23-5; Manufacturer PN SN74LVC1G32QDBVRQ1; Digikey 296-24202-6-ND
U25: LTC6993xS6-1; TSOT-23-6; Manufacturer PN LTC6993HS6-1#WTRMPBF; Digikey 505-LTC6993HS6-1#WTRMPBFDKR-ND; not fitted

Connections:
24V_RUN: D28.1 (A1), J5.1; also elsewhere on the board
+3.3V: C13.1, C15.1, C16.1, C17.1, C18.1, C34.1, C35.1, R30.2, R71.1, U4.5 (V+), U5.5 (VCC), U6.5 (VCC), U7.5 (VCC), U8.5 (VCC), U24.5 (VCC), U25.5 (V+); also elsewhere on the board
+24V: F13.2, F14.2, K2.14; also elsewhere on the board
FROM_SPAN: F3.2, J12.2
GND: C12.2, C13.2, C14.2, C15.2, C16.2, C17.2, C18.2, C19.2, C34.2, C35.2, D6.1 (A1), D8.2 (A2), D28.2 (A2), D33.2 (A2), D34.2 (A2), D36.2 (A2), J4.4, K1.A2, K3.A2, Q1.2 (S), R24.2, R25.2, R26.2, R28.2, R31.2, R33.2, R35.2, R67.2, R68.1, R69.2, R72.2, R73.2, R84.2, RV1.2, RV1.3, U4.2 (GND), U5.3 (GND), U6.3 (GND), U7.3 (GND), U8.3 (GND), U24.3 (GND), U25.2 (GND); also elsewhere on the board
L1: F10.1, K1.11; also elsewhere on the board
NEUTRAL: J13.1, K3.24; also elsewhere on the board
unnamed: C12.1, R23.2, R24.1, U5.2
unnamed: C14.1, R27.2, R28.1, U6.2
unnamed: C19.1, R70.2, R72.1, U8.2
unnamed: D7.1 (K), R35.1
unnamed: D33.1 (A1), J5.6, R22.1
unnamed: D34.1 (A1), J5.4, R25.1, R27.1
unnamed: D35.1 (K), R84.1
unnamed: F2.1, K3.11
unnamed: F3.1, K3.21
unnamed: F13.1, J4.1
unnamed: F14.1, J5.3, J5.5
unnamed: F10.2, J13.2
unnamed: K1.14, K2.A2
unnamed: K2.11, R70.1, R73.1
unnamed: K2.A1, K3.14
unnamed: Q1.3 (D), R22.2
unnamed: Q1.1 (G), R26.1, R29.1
unnamed: R32.2, RV1.1
unnamed: R102.2, U24.1
unnamed: R30.1, R33.1, U4.4 (DIV)
unnamed: R29.2, U4.1 (IN), U7.4
unnamed: R31.1, R32.1, U4.3 (SET)
unnamed: U7.2, U24.4
unnamed: R68.2, R71.2, U25.4 (DIV)
unnamed: U24.2, U25.6 (OUT)
unnamed: R69.1, U25.3 (SET)
REMOTE_ENABLE: D6.2 (A2), D8.1 (A1), D35.2 (A), D36.1 (A1), J4.2, J4.3, K1.A1, K3.A1, R23.1, TP5.1 (1_1); also elsewhere on the board
REMOTE_ENABLE_LOGIC_IN: U5.4; also elsewhere on the board
RUN_PWR: J5.2; also elsewhere on the board
SAFETY_BYPASS_LOGIC_IN: R102.1, U6.4; also elsewhere on the board
SAFETY_DELAY_LOGIC_IN: TP6.1 (1_1), U4.6 (OUT); also elsewhere on the board
SAFETY_IN: J12.4, K3.12
SAFETY_OUT: J12.1, K3.22
SAFETY_RAW_LOGIC_IN: D7.2 (A), TP7.1 (1_1), U7.1, U8.4; also elsewhere on the board
START: R67.1, U25.1 (TRIG); also elsewhere on the board
TO_SPAN: F2.2, J12.3

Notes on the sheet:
Switch
Safety Bypass Button w/Light
24V Lamp
External Local/Remote Switch w/Light
Button
FIT R31 or R32+RV1 - NOT BOTH RV1 wiper open → 551K → 23.1s
R31 ONLY 4s 95.3 kΩ 6s 143 kΩ 8s 191 kΩ 10s 237 kΩ 12s 287 kΩ 14s 332 kΩ

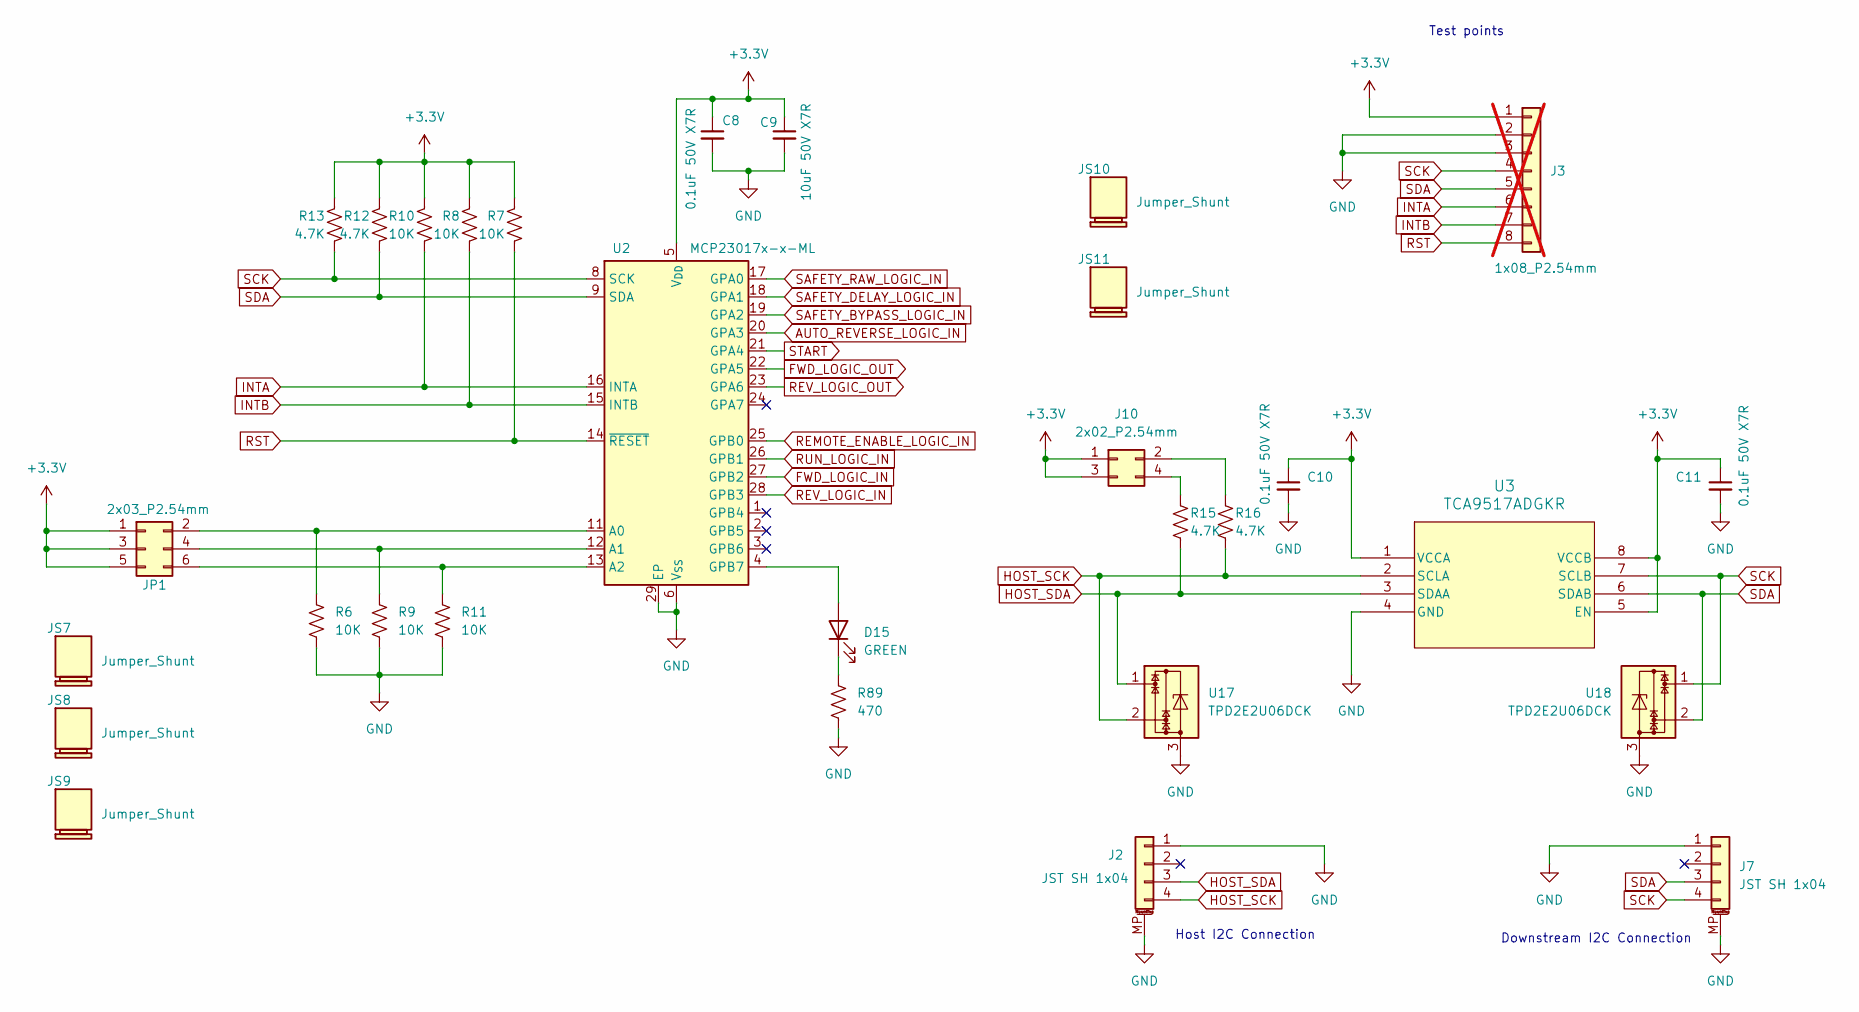
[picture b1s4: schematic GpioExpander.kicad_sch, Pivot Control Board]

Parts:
C8, C10, C11: 0.1uF 50V X7R; C_0603_1608Metric; Digikey 399-C0603C104K5RACTUDKR-ND
C9: 10uF 50V X7R; C_1210_3225Metric; Digikey 1276-7052-6-ND
D15: GREEN; LED_0603_1608Metric; Manufacturer PN 5991060147F; Digikey 350-5991060147FDKR-ND
J2, J7: JST SH 1x04; JST_SH_BM04B-SRSS-TB_1x04-1MP_P1.00mm_Vertical; Manufacturer PN BM04B-SRSS-TBT; Digikey 455-BM04B-SRSS-TBTDKR-ND
J3: 1x08_P2.54mm; PinHeader_1x08_P2.54mm_Vertical; Manufacturer PN 61300811121; Digikey 732-5321-ND; not fitted
J10: 2x02_P2.54mm; PinHeader_2x02_P2.54mm_Vertical; Manufacturer PN 61300421121; Digikey 732-5294-ND
JP1: 2x03_P2.54mm; PinHeader_2x03_P2.54mm_Vertical; Manufacturer PN 61300621121; Digikey 732-5295-ND
JS7, JS8, JS9, JS10, JS11: Jumper_Shunt; Manufacturer PN SPC02SYAN; Digikey S9001-ND
R6, R7, R8, R9, R10, R11: 10K; R_0603_1608Metric; Digikey 311-10KLDDKR-ND
R12, R13, R15, R16: 4.7K; R_0603_1608Metric; Digikey 311-4.70KHRDKR-ND
R89: 470; R_0603_1608Metric; Digikey 311-470HRDKR-ND
U2: MCP23017x-x-ML; QFN-28-1EP_6x6mm_P0.65mm_EP4.25x4.25mm; Manufacturer PN MCP23017T-E/ML; Digikey MCP23017T-E/MLDKR-ND
U3: TCA9517ADGKR; DGK8_TEX; Manufacturer PN TCA9517ADGKR; Digikey 296-39220-6-ND
U17, U18: TPD2E2U06DCK; SOT-323_SC-70; Manufacturer PN TPD2E2U06QDCKRQ1; Digikey 296-44302-6-ND

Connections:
+3.3V: C8.1, C9.1, C10.1, C11.1, J3.1, J10.1, J10.3, JP1.1, JP1.3, JP1.5, R7.1, R8.1, R10.1, R12.1, R13.1, U2.5 (V_{DD}), U3.1 (VCCA), U3.5 (EN), U3.8 (VCCB); also elsewhere on the board
AUTO_REVERSE_LOGIC_IN: U2.20 (GPA3); also elsewhere on the board
FWD_LOGIC_IN: U2.27 (GPB2); also elsewhere on the board
FWD_LOGIC_OUT: U2.22 (GPA5); also elsewhere on the board
GND: C8.2, C9.2, C10.2, C11.2, J2.1, J2.MP (MountPin), J3.2, J3.3, J7.1, J7.MP (MountPin), R6.2, R9.2, R11.2, R89.2, U2.6 (V_{SS}), U2.29 (EP), U3.4 (GND), U17.3, U18.3; also elsewhere on the board
HOST_SCK: J2.4, R16.2, U3.2 (SCLA), U17.2
HOST_SDA: J2.3, R15.2, U3.3 (SDAA), U17.1
INTA: J3.6, R10.2, U2.16 (INTA)
INTB: J3.7, R8.2, U2.15 (INTB)
unnamed: D15.2 (A), U2.4 (GPB7)
unnamed: D15.1 (K), R89.1
unnamed: J10.2, R16.1
unnamed: J10.4, R15.1
unnamed: JP1.2, R6.1, U2.11 (A0)
unnamed: JP1.4, R9.1, U2.12 (A1)
unnamed: JP1.6, R11.1, U2.13 (A2)
REMOTE_ENABLE_LOGIC_IN: U2.25 (GPB0); also elsewhere on the board
REV_LOGIC_IN: U2.28 (GPB3); also elsewhere on the board
REV_LOGIC_OUT: U2.23 (GPA6); also elsewhere on the board
RST: J3.8, R7.2, U2.14 (~RESET)
RUN_LOGIC_IN: U2.26 (GPB1); also elsewhere on the board
SAFETY_BYPASS_LOGIC_IN: U2.19 (GPA2); also elsewhere on the board
SAFETY_DELAY_LOGIC_IN: U2.18 (GPA1); also elsewhere on the board
SAFETY_RAW_LOGIC_IN: U2.17 (GPA0); also elsewhere on the board
SCK: J3.4, J7.4, R13.2, U2.8 (SCK), U3.7 (SCLB), U18.1
SDA: J3.5, J7.3, R12.2, U2.9 (SDA), U3.6 (SDAB), U18.2
START: U2.21 (GPA4); also elsewhere on the board

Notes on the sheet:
Downstream I2C Connection
Host I2C Connection
Test points
